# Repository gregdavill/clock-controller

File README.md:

# clockController

A simple breakout for a barebones flipdot display driver.

Features:
- ATSAMD11 32 bit MCU
- RTC with Super Cap Backup
- ublox GNSS (GPS + GLONASS), MAX-M8 part
- RS485 driver required by display
- User button for modes
- High input voltage DCDC buck stepdown
- Reverse Polarity Protection

Note this device has not been prototyped yet.

## 3d Render

## Schematic

## Development Timeline

- [x] Concept 
- [x] Schematic
- [x] PCB Layout
- [x] 3d CAD export/cleanup
- [x] BOM export
- [ ] Prototypes assembled
- [ ] Firmware buildup
- [ ] Additional Documentation
- [ ] Small Volume Run

## License

MIT - See [LICENCE](LICENSE)

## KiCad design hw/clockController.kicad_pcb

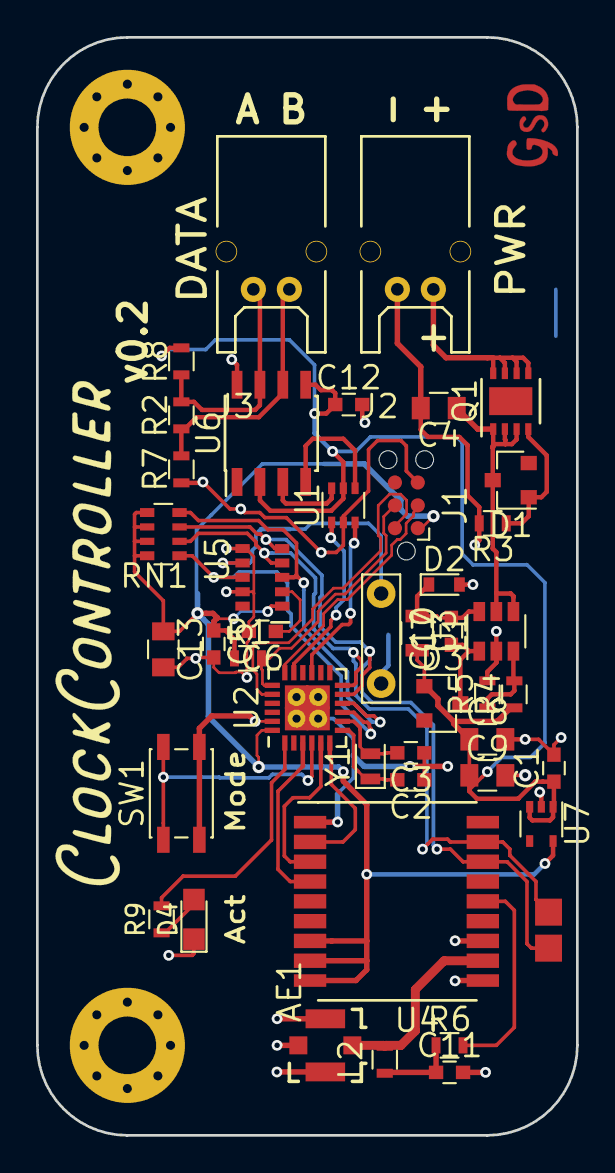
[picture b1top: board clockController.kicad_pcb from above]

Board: 2 copper layers, 30.0 x 61.0 mm, 43 parts (0 on the bottom side), 35 nets.

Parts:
AE1: IPX; MCRF
C1, C5, C7, C12: 100n; C_0603
C2, C3: 9pF; C_0603
C4: 1uF; C_0805
C6: 47pF; C_0603
C8, C9, C13: 10uF; C_0805
C10: 470mF; C_Rect_L7.0mm_W2.0mm_P5.00mm
C11: 10n; C_0603
D1: 10V; SOT-23
D2: 45V 200mA; D_0603
D3: D; D_SOT-23_ANK
D4: LED; LED_0805
J1: TC2030-CTX; Tag-Connect_TC2030-IDC-NL
J2, J3: JST S02B-PASK; SB02B-PASK-2
L1: 15uH; L_0805
L2: 47nH; L_0603
Q1: AON7407; DFN-8-1EP_3x3mm_Pitch0.65mm
R1: 1K; R_0603
R2: 120R; R_0603
R3, R5: 10K; R_0603
R4: 52.3K; R_0603
R6: 10R; R_0603
R7, R8, R9: 680R; R_0603
RN1: 4.7K; R_Array_Convex_4x0603
SW1: TACT_SW; SW_SPST_EVQP2
U1: SN74LVC2G17; SOT-363_SC-70-6
U2: ATSAMD11D14A; QFN-24-1EP_4x4mm_Pitch0.5mm
U3: MCP16301; SOT-23-6
U4: MAX_M8Q; MAX_M8
U5: AB-RTCMC; 10-DFN
U6: SN65176B; SOIC-8_3.9x4.9mm_Pitch1.27mm
U7: MIC5365; SOT-353_SC-70-5
Y1: 32.768kHz; Crystal_SMD_2012-2pin_2.0x1.2mm

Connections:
+3V3: C5.1, C13.1, J1.1, R1.1, RN1.5, RN1.6, RN1.7, RN1.8, U2.24, U4.7, U4.8, U4.9, U5.1, U7.5
+5V: C1.1, C8.1, C9.1, C12.1, D3.2, L1.2, R4.1, R8.2, U1.5, U6.2, U6.5, U7.1, U7.3
/RS485_A: J3.2, R2.2, R8.1, U6.7
/RS485_B: J3.1, R2.1, R7.2, U6.6
BUTTON: SW1.1, U2.4
CTX_RST: J1.3, U2.18
CTX_SWCLK: J1.4, R1.2, U2.19
CTX_SWDIO: J1.2, U2.20
GND: AE1.2, C1.2, C2.1, C3.1, C4.2, C5.2, C6.2, C8.2, C9.2, C10.2, C11.2, C12.2, C13.2, D2.2, D4.1, J1.5, J2.2, R3.2, R5.2, R7.1, SW1.2, U1.2, U2.23, U2.25, U3.2, U4.1, U4.10, U4.12, U5.6, U5.9, U6.8, U7.2
GPS_PPS: U2.3, U4.4
GPS_RX: U2.6, U4.2
GPS_TX: U2.5, U4.3
I2C_SCL: RN1.2, U2.12, U4.17, U5.4
I2C_SDA: RN1.3, U2.11, U4.16, U5.5
LED_A: R9.2, U2.1
unnamed: AE1.1, L2.2, U4.11
unnamed: C2.2, U2.7, Y1.1
unnamed: C3.2, U2.8, Y1.2
unnamed: C4.1, D1.1, Q1.1, Q1.2, Q1.3, U3.4, U3.5
unnamed: C6.1, U5.2
unnamed: C7.1, D3.1, U3.1
unnamed: C7.2, D2.1, L1.1, U3.6
unnamed: C10.1, U5.7
unnamed: C11.1, L2.1, R6.1
unnamed: D1.2, Q1.4, R3.1
unnamed: D4.2, R9.1
unnamed: J2.1, Q1.5, Q1.6, Q1.7, Q1.8
unnamed: R4.2, R5.1, U3.3
unnamed: R6.2, U4.14
unnamed: U1.4, U6.4
unnamed: U1.6, U6.3
RS485_DATA: U1.3, U2.15
RS485_EN: U1.1, U2.17
RTC_INT1: RN1.4, U2.10, U5.3
RTC_INT2: RN1.1, U2.9, U5.8

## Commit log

2018-03-08 Added a very basic firmware project. Using Cmake and vs code.
2018-07-29 Update kicad project, and samd11 firmware.
